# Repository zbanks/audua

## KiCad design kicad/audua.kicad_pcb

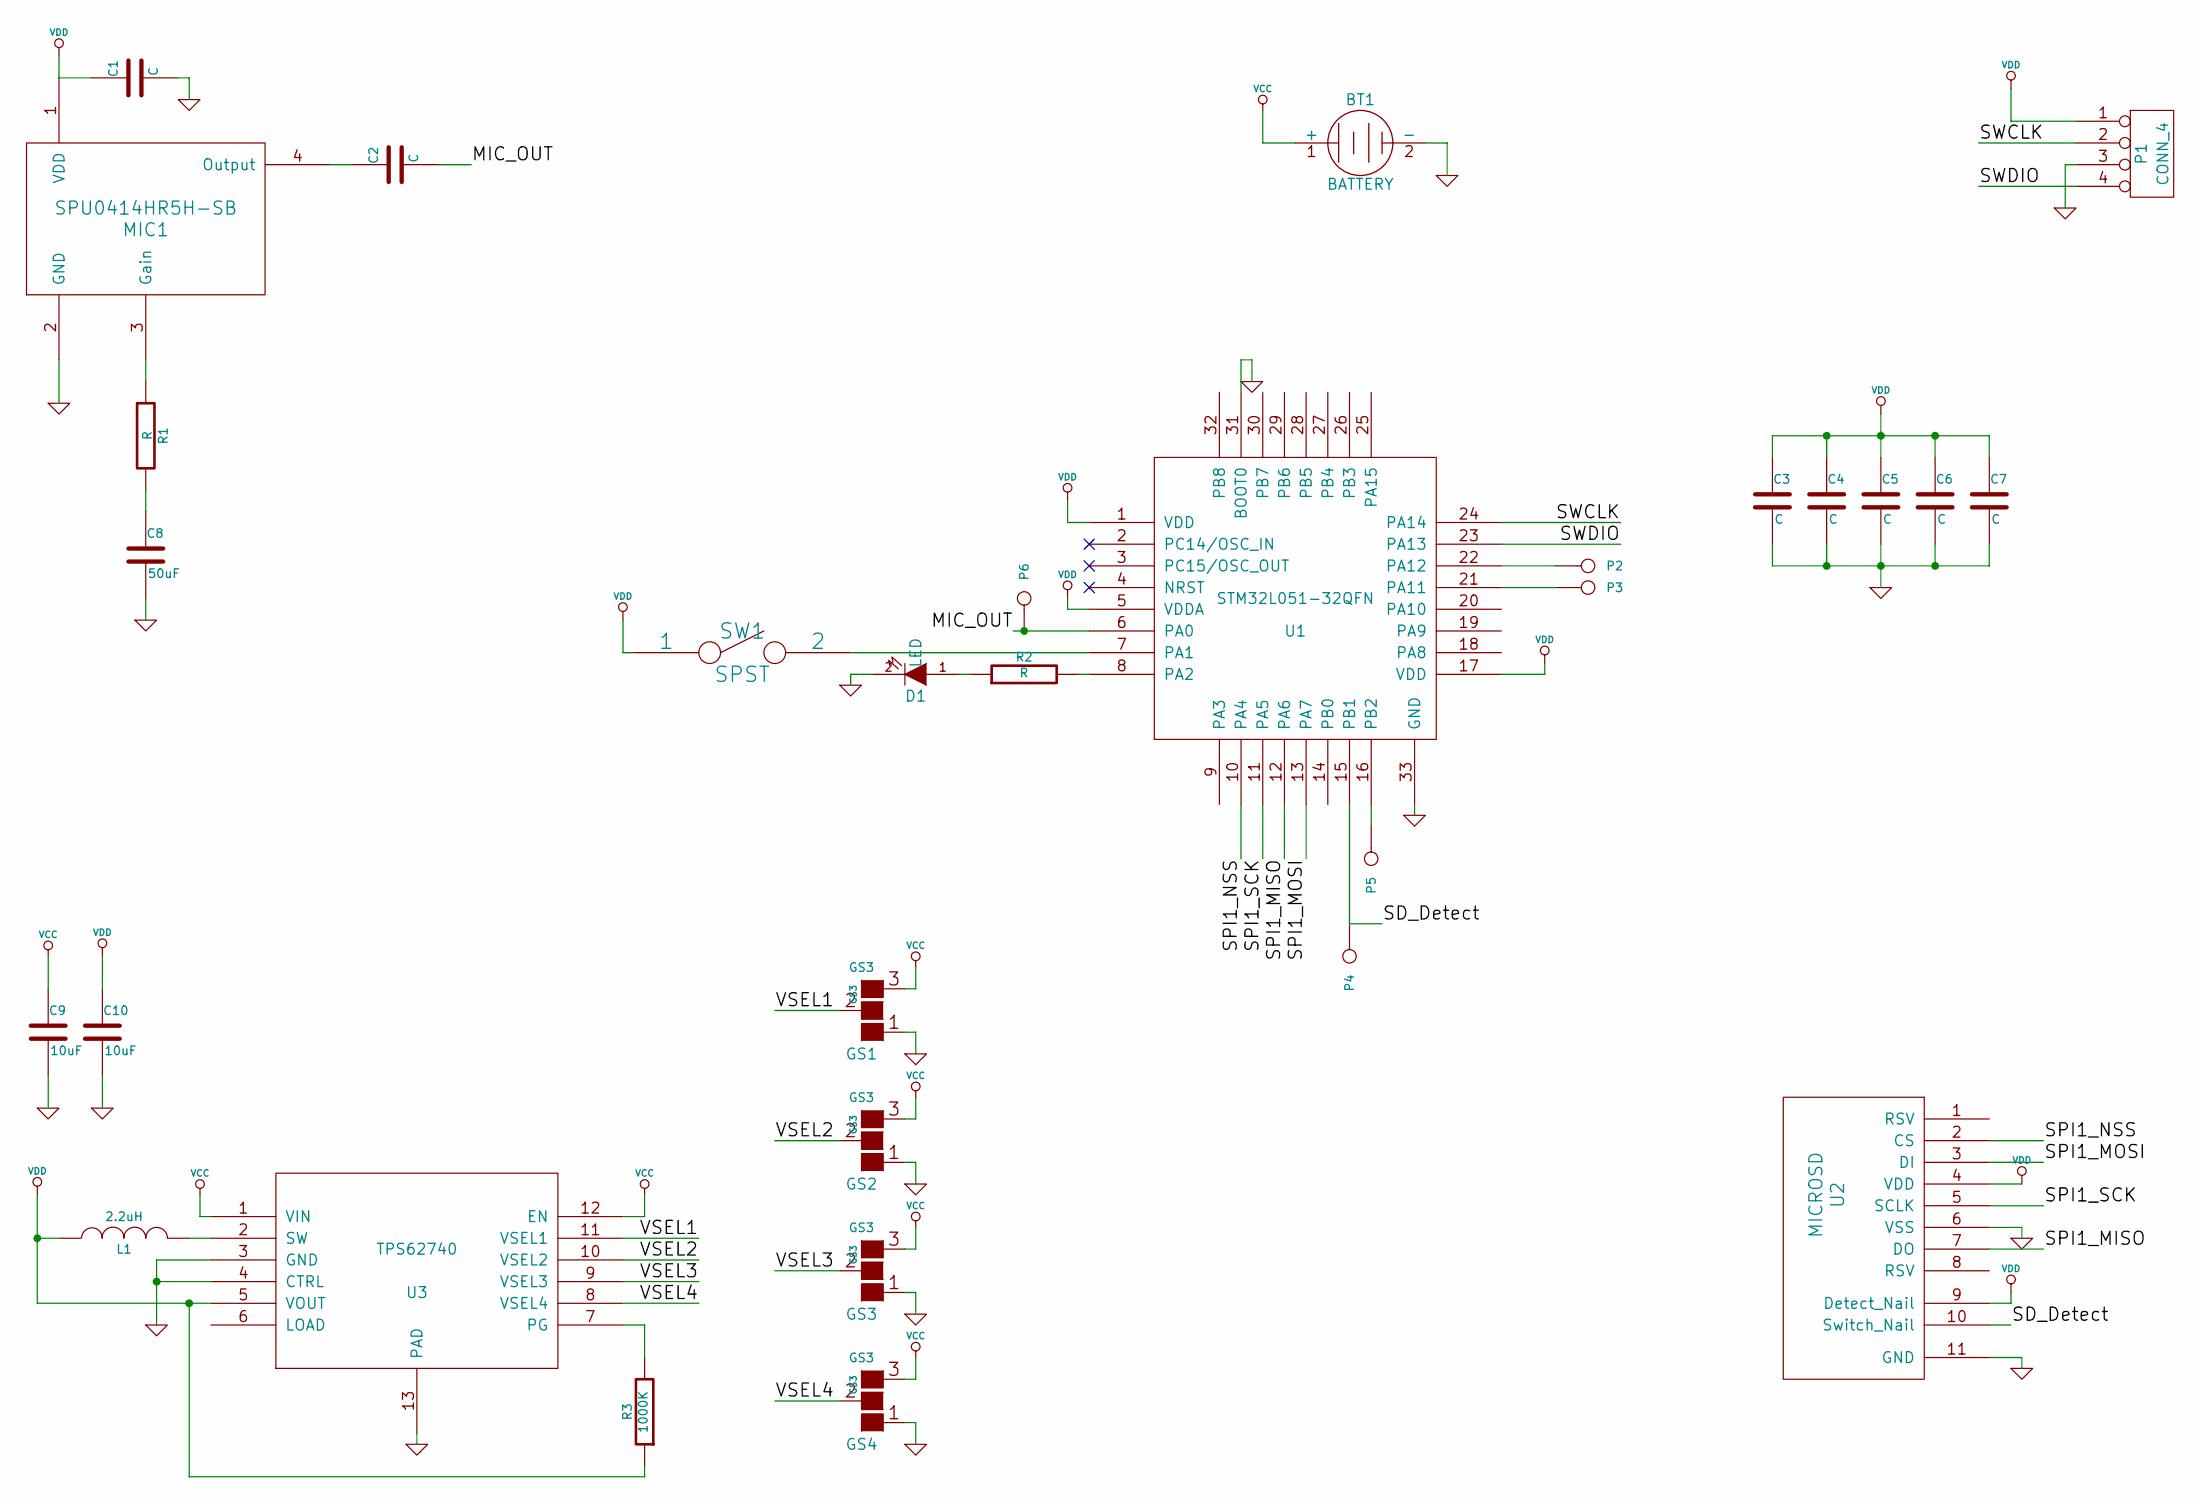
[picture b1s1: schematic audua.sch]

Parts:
BT1: BATTERY
C1, C2, C3, C4, C5, C6, C7: C
C8: 50uF
C9, C10: 10uF
D1: LED
GS1, GS2, GS3, GS4: GS3
L1: 2.2uH
MIC1: SPU0414HR5H-SB
P1: CONN_4
P2, P3, P4, P5, P6: CONN_1
R1, R2: R
R3: 1000K
SW1: SPST
U1: STM32L051-32QFN; MODULE
U2: MICROSD
U3: TPS62740; MODULE

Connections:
/MIC_OUT: C2.2, P6.1, U1.6 (PA0)
/SPI1_MISO: U1.12 (PA6), U2.7 (DO)
/SPI1_MOSI: U1.13 (PA7), U2.3 (DI)
/SPI1_NSS: U1.10 (PA4), U2.2 (CS)
/SPI1_SCK: U1.11 (PA5), U2.5 (SCLK)
/SWCLK: P1.2, U1.24 (PA14)
/SWDIO: P1.4, U1.23 (PA13)
/VSEL1: GS1.2 (G2), U3.11 (VSEL1)
/VSEL2: GS2.2 (G2), U3.10 (VSEL2)
/VSEL3: GS3.2 (G2), U3.9 (VSEL3)
/VSEL4: GS4.2 (G2), U3.8 (VSEL4)
GND: BT1.2 (-), C1.2, C3.2, C4.2, C5.2, C6.2, C7.2, C8.2, C9.2, C10.2, D1.2 (K), GS1.1 (G1), GS2.1 (G1), GS3.1 (G1), GS4.1 (G1), MIC1.2 (GND), P1.3, U1.31 (BOOT0), U1.33 (GND), U2.6 (VSS), U2.11 (GND), U3.3 (GND), U3.4 (CTRL), U3.13 (PAD)
unnamed: L1.2, U3.2 (SW)
unnamed: R3.2, U3.7 (PG)
unnamed: R2.2, U1.8 (PA2)
unnamed: D1.1 (A), R2.1
unnamed: C2.1, MIC1.4 (Output)
unnamed: MIC1.3 (Gain), R1.1
unnamed: C8.1, R1.2
unnamed: P5.1, U1.16 (PB2)
unnamed: P4.1, U1.15 (PB1), U2.10 (Switch_Nail)
unnamed: P3.1, U1.21 (PA11)
unnamed: P2.1, U1.22 (PA12)
unnamed: SW1.2, U1.7 (PA1)
VCC: BT1.1 (+), C9.1, GS1.3 (G3), GS2.3 (G3), GS3.3 (G3), GS4.3 (G3), U3.1 (VIN), U3.12 (EN)
VDD: C1.1, C3.1, C4.1, C5.1, C6.1, C7.1, C10.1, L1.1, MIC1.1 (VDD), P1.1, R3.1, SW1.1, U1.1 (VDD), U1.5 (VDDA), U1.17 (VDD), U2.4 (VDD), U2.9 (Detect_Nail), U3.5 (VOUT)

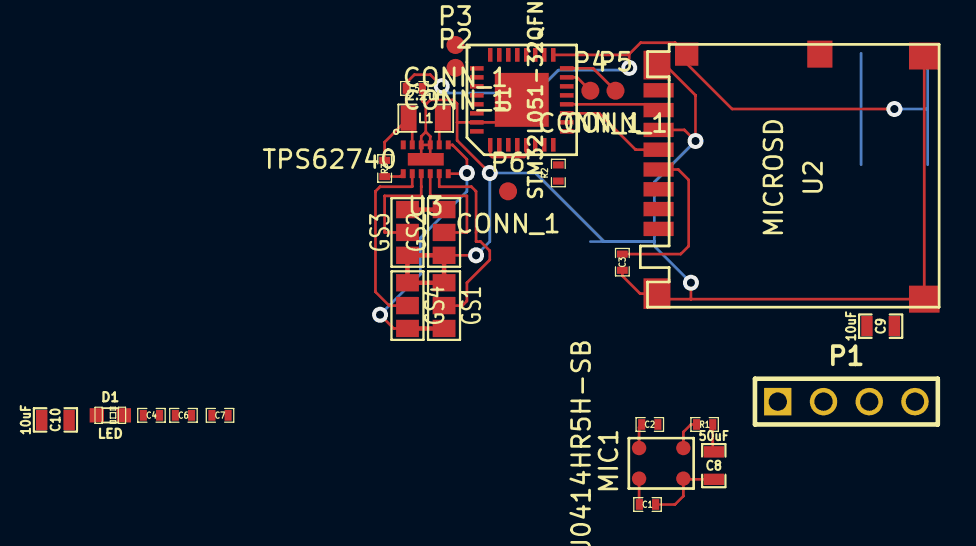
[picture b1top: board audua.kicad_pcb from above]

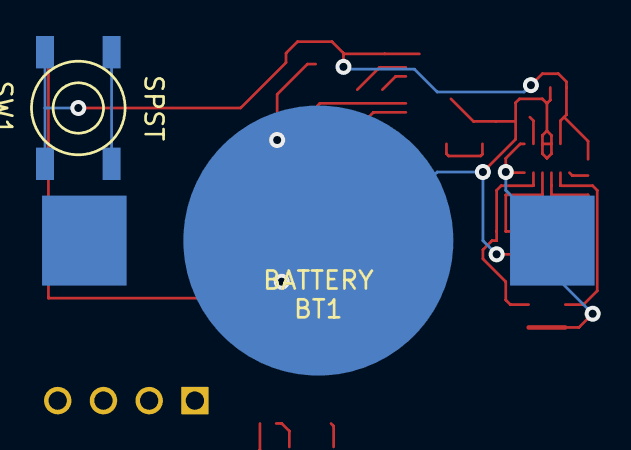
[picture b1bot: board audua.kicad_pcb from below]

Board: 2 copper layers, 31 parts (2 on the bottom side), 26 nets.

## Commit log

2014-06-14 Initial commit until @vinitlee told me to stop
2014-06-14 Most things
2014-06-14 Added buck converter
2014-06-14 Libraries
2014-06-24 Not Sure.
2014-08-01 Done?!
